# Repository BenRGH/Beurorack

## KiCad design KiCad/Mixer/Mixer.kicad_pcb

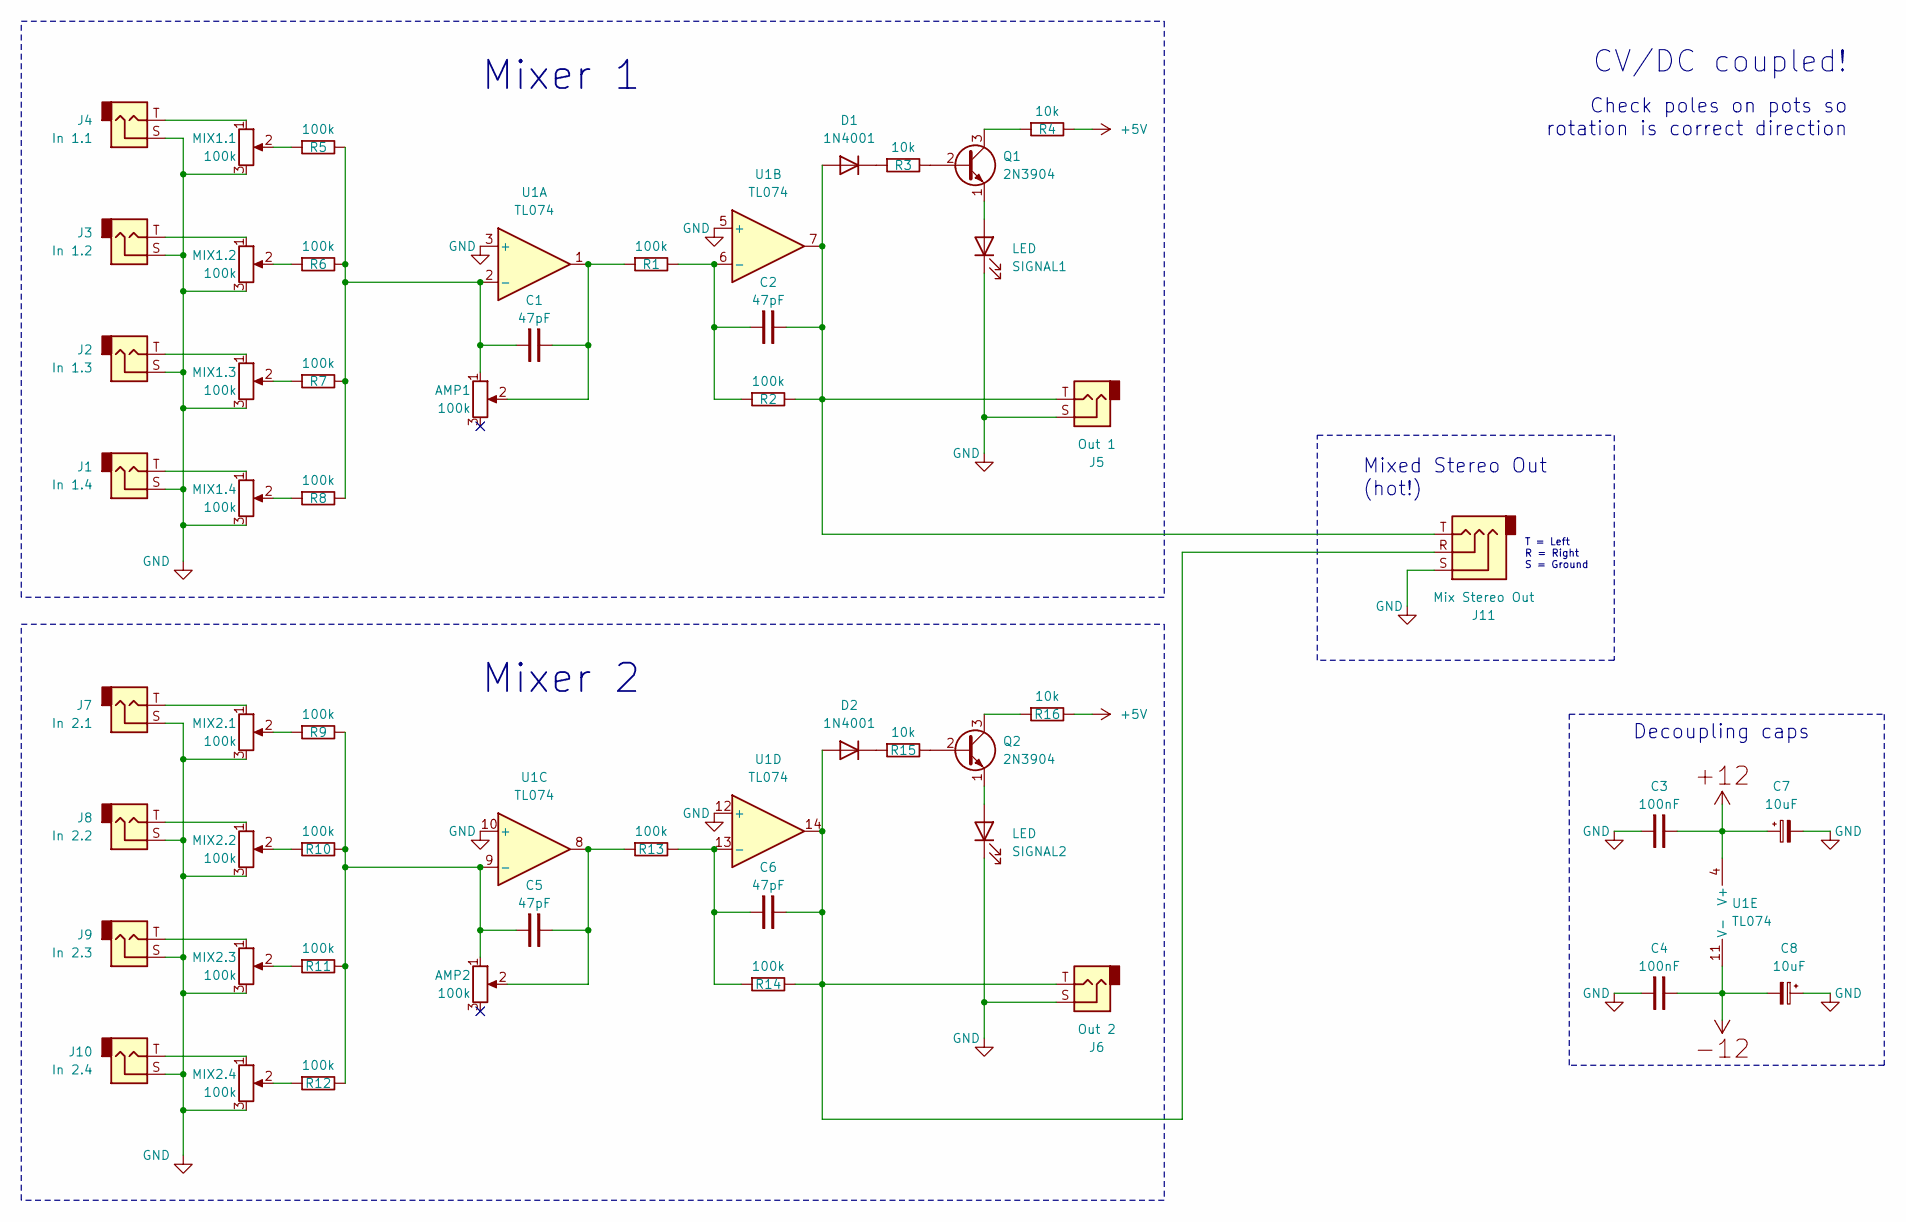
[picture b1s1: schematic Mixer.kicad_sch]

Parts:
AMP1, AMP2: 100k; Pot_9mm_DShaft
C1, C2, C5, C6: 47pF; C_Disc_D3.0mm_W2.0mm_P2.50mm
C3, C4: 100nF; C_Disc_D3.0mm_W2.0mm_P2.50mm
C7, C8: 10uF; CP_Radial_P2.5mm
D1, D2: 1N4001; D_DO-41_SOD81_P10.16mm_Horizontal
J1: In 1.4; Jack_6.35mm_Neutrik_NJ2FD-V_Vertical
J2: In 1.3; Jack_6.35mm_Neutrik_NJ2FD-V_Vertical
J3: In 1.2; Jack_6.35mm_Neutrik_NJ2FD-V_Vertical
J4: In 1.1; Jack_6.35mm_Neutrik_NJ2FD-V_Vertical
J5: Out 1; Jack_6.35mm_Neutrik_NJ2FD-V_Vertical
J6: Out 2; Jack_6.35mm_Neutrik_NJ2FD-V_Vertical
J7: In 2.1; Jack_6.35mm_Neutrik_NJ2FD-V_Vertical
J8: In 2.2; Jack_6.35mm_Neutrik_NJ2FD-V_Vertical
J9: In 2.3; Jack_6.35mm_Neutrik_NJ2FD-V_Vertical
J10: In 2.4; Jack_6.35mm_Neutrik_NJ2FD-V_Vertical
J11: Mix Stereo Out; Jack_6.35mm_Neutrik_NJ3FD-V_Vertical
MIX1.1, MIX1.2, MIX1.3, MIX1.4, MIX2.1, MIX2.2, MIX2.3, MIX2.4: 100k; Pot_9mm_DShaft
Q1, Q2: 2N3904; TO-92_Inline
R1, R2, R5, R6, R7, R8, R9, R10, R11, R12, R13, R14: 100k; R_Axial_DIN0207_L6.3mm_D2.5mm_P10.16mm_Horizontal
R3, R4, R15, R16: 10k; R_Axial_DIN0207_L6.3mm_D2.5mm_P10.16mm_Horizontal
SIGNAL1, SIGNAL2: LED; LED_3mm_C1A2_Polarity_Indicator
U1: TL074; DIP-14_W7.62mm

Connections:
+5V: R4.2, R16.2
+10: C3.2, C7.1, U1.4 (V+)
-12: C4.2, C8.2, U1.11 (V-)
GND: C3.1, C4.1, C7.2, C8.1, J1.S, J2.S, J3.S, J4.S, J5.S, J6.S, J7.S, J8.S, J9.S, J10.S, J11.S, MIX1.1.3, MIX1.2.3, MIX1.3.3, MIX1.4.3, MIX2.1.3, MIX2.2.3, MIX2.3.3, MIX2.4.3, SIGNAL1.1 (K), SIGNAL2.1 (K), U1.3 (+), U1.5 (+), U1.10 (+), U1.12 (+)
unnamed: AMP1.2, C1.2, R1.1, U1.1
unnamed: AMP2.2, C5.2, R13.1, U1.8
unnamed: C2.2, D1.2 (A), J5.T, J11.T, R2.2, U1.7
unnamed: D1.1 (K), R3.1
unnamed: C6.2, D2.2 (A), J6.T, J11.R, R14.2, U1.14
unnamed: D2.1 (K), R15.1
unnamed: J1.T, MIX1.4.1
unnamed: J2.T, MIX1.3.1
unnamed: J3.T, MIX1.2.1
unnamed: J4.T, MIX1.1.1
unnamed: J7.T, MIX2.1.1
unnamed: J8.T, MIX2.2.1
unnamed: J9.T, MIX2.3.1
unnamed: J10.T, MIX2.4.1
unnamed: MIX1.1.2, R5.1
unnamed: MIX1.2.2, R6.1
unnamed: MIX1.3.2, R7.1
unnamed: MIX1.4.2, R8.1
unnamed: MIX2.1.2, R9.1
unnamed: MIX2.2.2, R10.1
unnamed: MIX2.3.2, R11.1
unnamed: MIX2.4.2, R12.1
unnamed: Q1.2 (B), R3.2
unnamed: Q1.3 (C), R4.1
unnamed: Q1.1 (E), SIGNAL1.2 (A)
unnamed: Q2.2 (B), R15.2
unnamed: Q2.3 (C), R16.1
unnamed: Q2.1 (E), SIGNAL2.2 (A)
unnamed: AMP1.1, C1.1, R5.2, R6.2, R7.2, R8.2, U1.2 (-)
unnamed: C2.1, R1.2, R2.1, U1.6 (-)
unnamed: AMP2.1, C5.1, R9.2, R10.2, R11.2, R12.2, U1.9 (-)
unnamed: C6.1, R13.2, R14.1, U1.13 (-)

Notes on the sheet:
Decoupling caps
T = Left R = Right S = Ground
Check poles on pots so rotation is correct direction
Mixed Stereo Out (hot!)
CV/DC coupled!
Mixer 2
Mixer 1

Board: 2 copper layers, 53 parts (1 on the bottom side), 36 nets, no tracks yet.

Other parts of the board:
H5: POWER; Pins_2x05_2.54mm_TH_Europower

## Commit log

2024-10-29 init
2024-10-29 tidy and add circuits
2024-11-03 Mixer Schematic V1
2024-11-03 Arranged mixer footprints
2024-11-04 Mixer PCB WIP
